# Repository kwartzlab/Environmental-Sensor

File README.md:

# Kwartzlab Environmental Sensor

The Kwartzlab Environemntal Sensor is a sensor board that is powered by an ESP32 which sends environmental metrics to grafana over wifi.

## Sensors
* [SHTC3 Humidity and Temperature Sensor](datasheets/SHTC3.pdf)
* [BME688 Gas Sensor](datasheets/BME688.pdf)
* [SPS30 Air Quality Sensor](datasheets/SPS30.pdf)
* [Zio Loudness Sensor](https://www.smart-prototyping.com/blog/Zio-Loudness-Sensor-Qwiic-Start-Guide)

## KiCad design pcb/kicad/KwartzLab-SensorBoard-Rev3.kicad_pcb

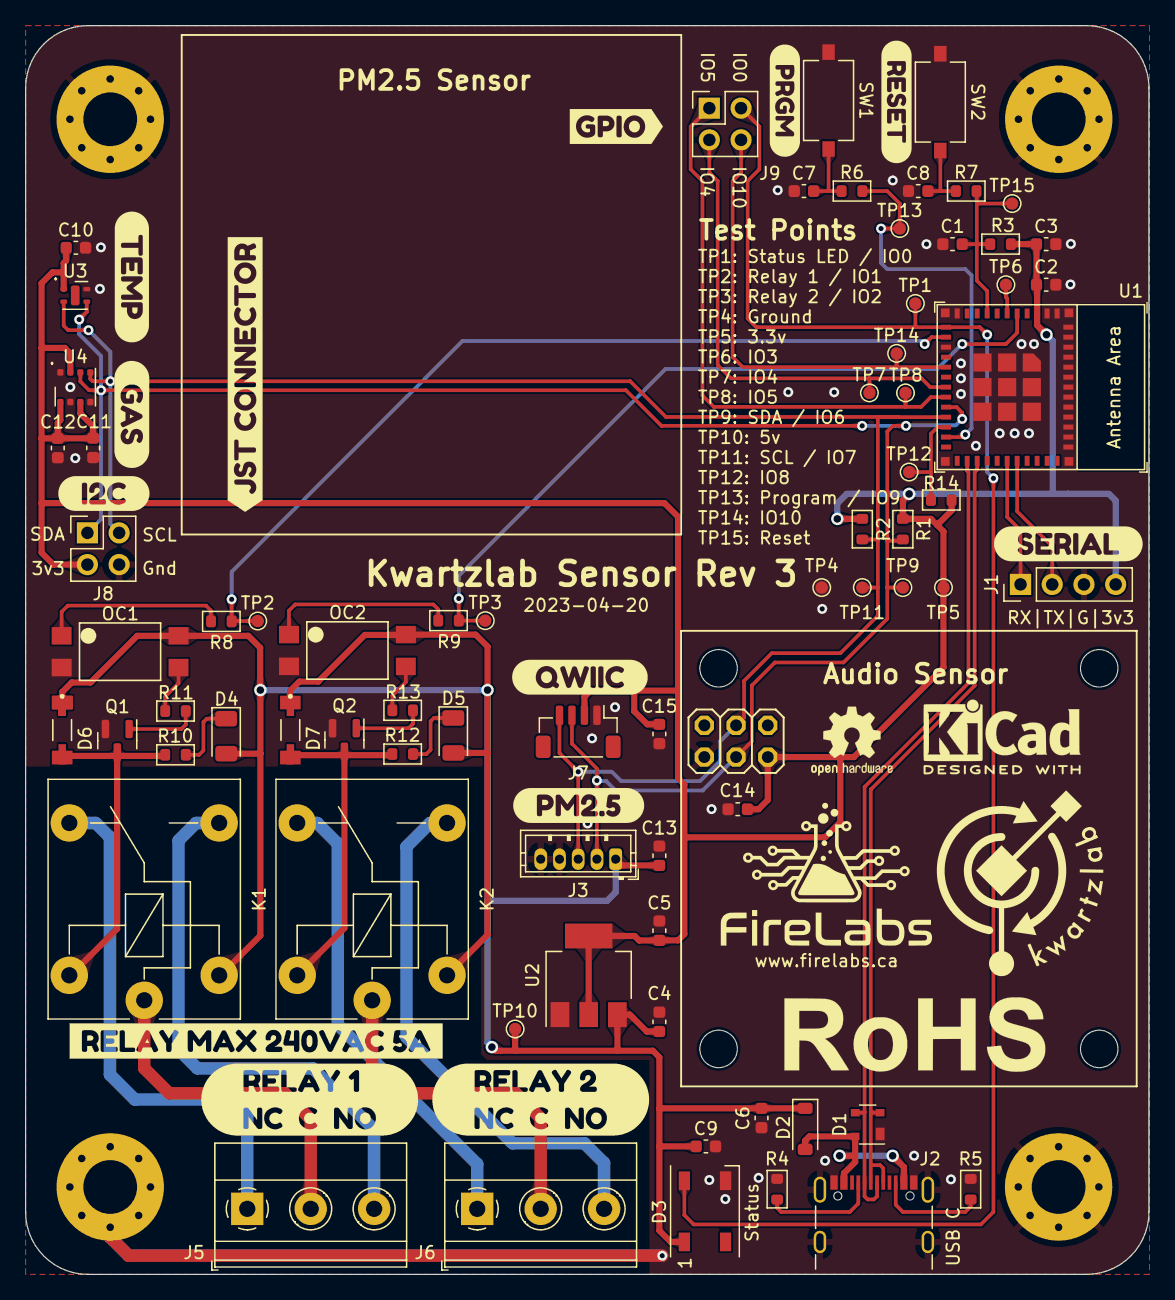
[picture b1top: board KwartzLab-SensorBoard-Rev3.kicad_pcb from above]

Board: 2 copper layers, 90.0 x 100.0 mm, 89 parts (0 on the bottom side), 40 nets.

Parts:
C1: 1uF / 16v (10%); C_0603_1608Metric
C2, C4, C5, C6, C9, C10, C11, C12, C13, C14, C15: 10uF / 25v (20%); C_0603_1608Metric
C3: 0.1uF / 50v (10%); C_0603_1608Metric
C7, C8: 0.1uF / 50v (10%) (NC); C_0603_1608Metric
D1: SP0503BAHT; SOT-143
D2: 1N5819HW-7-F; D_SOD-123
D3: WS2812B; LED_WS2812B_PLCC4_5.0x5.0mm_P3.2mm
D4, D5: LED; LED_1206_3216Metric
D6, D7: LL4148; DIO_LL4148
H1, H2, H3, H4: M4; MountingHole_4.3mm_M4_Pad_Via
J1: Serial Interface; PinHeader_1x04_P2.54mm_Vertical
J2: USB_C_Receptacle_USB2.0; USB_C_Receptacle_GCT_USB4105-xx-A_16P_TopMnt_Horizontal
J3: PM2.5 Sensor; JST_ZH_B5B-ZR_1x05_P1.50mm_Vertical
J4: Zio Loudness Sensor; zio_loudness_sensor
J5, J6: Screw_Terminal_01x03; TerminalBlock_Phoenix_MKDS-1,5-3-5.08_1x03_P5.08mm_Horizont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
J7: Qwiic Connector; JST_SH_BM04B-SRSS-TB_1x04-1MP_P1.00mm_Vertical
J8, J9: Conn_02x02_Odd_Even; PinHeader_2x02_P2.54mm_Vertical
K1, K2: 5v Relay; Relay_SPDT_Finder_36.11
OC1, OC2: APC-817A1; SMD4-2.54-4.6X6.5MM
Q1, Q2: MMBT3904; SOT-23
R1, R2: 5.1k (1%); R_0603_1608Metric
R3, R14: 10k (1%); R_0603_1608Metric
R4, R5: 5.11k; R_0603_1608Metric
R6, R7: 100; R_0603_1608Metric
R8, R9, R10, R12: 1k (1%); R_0603_1608Metric
R11, R13: 470 (1%); R_0603_1608Metric
SW1, SW2: SW_Push; SW_Tactile_SPST_NO_Straight_CK_PTS636Sx25SMTRLFS
TP1: Status; TestPoint_Pad_D1.0mm
TP2: Relay 1; TestPoint_Pad_D1.0mm
TP3: Relay 2; TestPoint_Pad_D1.0mm
TP4: GND; TestPoint_Pad_D1.0mm
TP5: 3V3; TestPoint_Pad_D1.0mm
TP6: GPIO3; TestPoint_Pad_D1.0mm
TP7: GPIO4; TestPoint_Pad_D1.0mm
TP8: GPIO5; TestPoint_Pad_D1.0mm
TP9: SDA; TestPoint_Pad_D1.0mm
TP10: 5V; TestPoint_Pad_D1.0mm
TP11: SCL; TestPoint_Pad_D1.0mm
TP12: GPIO8; TestPoint_Pad_D1.0mm
TP13: Program; TestPoint_Pad_D1.0mm
TP14: GPIO10; TestPoint_Pad_D1.0mm
TP15: Reset; TestPoint_Pad_D1.0mm
U1: ESP32-C3-MINI-1
U2: AMS1117-3.3; SOT-223-3_TabPin2
U3: SHTC3; Sensirion_DFN-4-1EP_2x2mm_P1mm_EP0.7x1.6mm
U4: BME688; Bosch_LGA-8_3x3mm_P0.8mm_ClockwisePinNumbering
kibuzzard-64420A01: G***; kibuzzard-64420A01
kibuzzard-64420A6A: G***; kibuzzard-64420A6A
kibuzzard-64420C1B: G***; kibuzzard-64420C1B
kibuzzard-64420C5E: G***; kibuzzard-64420C5E
kibuzzard-64420C16: G***; kibuzzard-64420C16
kibuzzard-64420C24: G***; kibuzzard-64420C24
kibuzzard-64420C54: G***; kibuzzard-64420C54
kibuzzard-64420CBE: G***; kibuzzard-64420CBE
kibuzzard-64420CCA: G***; kibuzzard-64420CCA
kibuzzard-64420E8B: G***; kibuzzard-64420E8B
kibuzzard-644209FA: G***; kibuzzard-644209FA
kibuzzard-644479D4: G***; kibuzzard-644479D4
kibuzzard-64444232: G***; kibuzzard-64444232

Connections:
+3V3: C2.1, C3.1, C5.1, C10.1, C11.1, C12.1, C14.1, C15.2, J1.4, J4.2, J7.2, J8.3, R1.1, R2.1, R3.1, R14.2, TP5.1, U1.3 (3V3), U2.2 (VO), U3.1 (VDD), U4.2 (CSB), U4.6 (VDDIO), U4.8 (VDD)
+5V: C4.1, C6.1, C9.1, C13.1, D2.1 (K), D3.1 (VDD), D4.2 (A), D5.2 (A), D6.1, D7.1, J3.1, K1.A1, K2.A1, OC1.4, OC2.4, TP10.1, U2.3 (VI)
/Output Relays/RELAY1_COM: J5.2, K1.11
/Output Relays/RELAY1_EN: D6.2, K1.A2, Q1.3 (C), R10.2
/Output Relays/RELAY1_NC: J5.1, K1.12
/Output Relays/RELAY1_NO: J5.3, K1.14
/Output Relays/RELAY1_STATUS_LED: D4.1 (K), R10.1
/Output Relays/RELAY2_COM: J6.2, K2.11
/Output Relays/RELAY2_EN: D7.2, K2.A2, Q2.3 (C), R12.2
/Output Relays/RELAY2_NC: J6.1, K2.12
/Output Relays/RELAY2_NO: J6.3, K2.14
/Output Relays/RELAY2_STATUS_LED: D5.1 (K), R12.1
/RX: J1.1, U1.30 (GPIO20/U0RXD)
/TX: J1.2, U1.31 (GPIO21/U0TXD)
/USB C Connector/USB_CC1: J2.A5 (CC1), R4.2
/USB C Connector/USB_CC2: J2.B5 (CC2), R5.2
/USB_DN: D1.3 (L2), J2.A7 (D-), J2.B7 (D-), U1.26 (GPIO18/USB_D-)
/USB_DP: D1.2 (L1), J2.A6 (D+), J2.B6 (D+), U1.27 (GPIO19/USB_D+)
BOOT: R6.2, TP13.1, U1.23 (GPIO9)
GND: C1.1, C2.2, C3.2, C4.2, C5.2, C6.2, C7.1, C8.1, C9.2, C10.2, C11.2, C12.2, C13.2, C14.2, C15.1, D1.1 (VN), D3.3 (VSS), H1.1, H2.1, H3.1, H4.1, J1.3, J2.A1 (GND), J2.A12 (GND), J2.B1 (GND), J2.B12 (GND), J2.S1 (SHIELD), J3.4, J3.5, J4.6, J7.1, J8.4, OC1.2, OC2.2, Q1.2 (E), Q2.2 (E), R4.1, R5.1, SW1.1, SW2.1, TP4.1, U1.1 (GND), U1.2 (GND), U1.11 (GND), U1.14 (GND), U1.36 (GND), U1.37 (GND), U1.38 (GND), U1.39 (GND), U1.40 (GND), U1.41 (GND), U1.42 (GND), U1.43 (GND), U1.44 (GND), U1.45 (GND), U1.46 (GND), U1.47 (GND), U1.48 (GND), U1.49 (GND), U1.50 (GND), U1.51 (GND), U1.52 (GND), U1.53 (GND), U2.1 (GND), U3.4 (VSS), U4.1 (GND), U4.5 (SDO), U4.7 (GND)
GPIO3: TP6.1, U1.6 (GPIO3/ADC1_CH3)
GPIO4: J9.3, TP7.1, U1.18 (GPIO4/ADC1_CH4)
GPIO5: J9.1, TP8.1, U1.19 (GPIO5/ADC2_CH0)
GPIO8: R14.1, TP12.1, U1.22 (GPIO8)
GPIO10: J9.4, TP14.1, U1.16 (GPIO10)
unnamed: C7.2, R6.1, SW1.2
unnamed: C8.2, R7.1, SW2.2
unnamed: OC1.1, R8.2
unnamed: OC1.3, R11.2
unnamed: OC2.1, R9.2
unnamed: OC2.3, R13.2
unnamed: Q1.1 (B), R11.1
unnamed: Q2.1 (B), R13.1
RELAY1: R8.1, TP2.1, U1.13 (GPIO1/ADC1_CH1/XTAL_32K_N)
RELAY2: R9.1, TP3.1, U1.5 (GPIO2/ADC1_CH2)
RESET: C1.2, R3.2, R7.2, TP15.1, U1.8 (EN/CHIP_PU)
SCL: J3.3, J4.3, J7.4, J8.2, R2.2, TP11.1, U1.21 (GPIO7), U3.2 (SCL), U4.4 (SCK)
SDA: J3.2, J4.4, J7.3, J8.1, R1.2, TP9.1, U1.20 (GPIO6), U3.3 (SDA), U4.3 (SDI)
STATUS: D3.4 (DIN), J9.2, TP1.1, U1.12 (GPIO0/ADC1_CH0/XTAL_32K_P)
VBUS: D1.4 (L3), D2.2 (A), J2.A4 (VBUS), J2.A9 (VBUS), J2.B4 (VBUS), J2.B9 (VBUS)

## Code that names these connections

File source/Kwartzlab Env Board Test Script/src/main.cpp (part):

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#define TOTAL_LEDS 1

// GPIO Pins
#define RELAY1 1
#define RELAY2 2
#define GPIO3 3
#define GPIO4 4
#define GPIO5 5
#define I2C_SDA 6
#define I2C_SCL 7
#define GPIO8 8
#define PROGRAM_BUTTON 9
#define GPIO10 10

// I2C Addresses
#define SEGMENT_DISPLAY_1 0x71
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  while (!Serial) delay(2000);

  // Setup Relay GPIO Pins
  pinMode(RELAY1, OUTPUT); // Relay 1
  pinMode(RELAY2, OUTPUT); // Relay 2

  // Setup Generic GPIO Pins
  pinMode(GPIO3, OUTPUT); // GPIO3
  pinMode(GPIO4, OUTPUT); // GPIO4
  pinMode(GPIO5, OUTPUT); // GPIO5
  pinMode(GPIO8, OUTPUT); // GPIO6
  pinMode(GPIO10, OUTPUT); // GPIO10

  delay(5000);

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
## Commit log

2023-03-25 initial upload
2023-03-25 added codeowners file
2023-03-25 adding bom for the board and panel
2023-04-09 Rev 2 Update
    Change Log:
    - added I2C header
    - added GPIO header (IO0, IO4, IO5, IO10)
    - added 10k pull-up on IO8
    - added label on USB C port
    - added kwartzlab logo to the silk screen layer
2023-04-23 rev3-update
2023-04-23 updated a few parts
2023-05-07 finished test script
